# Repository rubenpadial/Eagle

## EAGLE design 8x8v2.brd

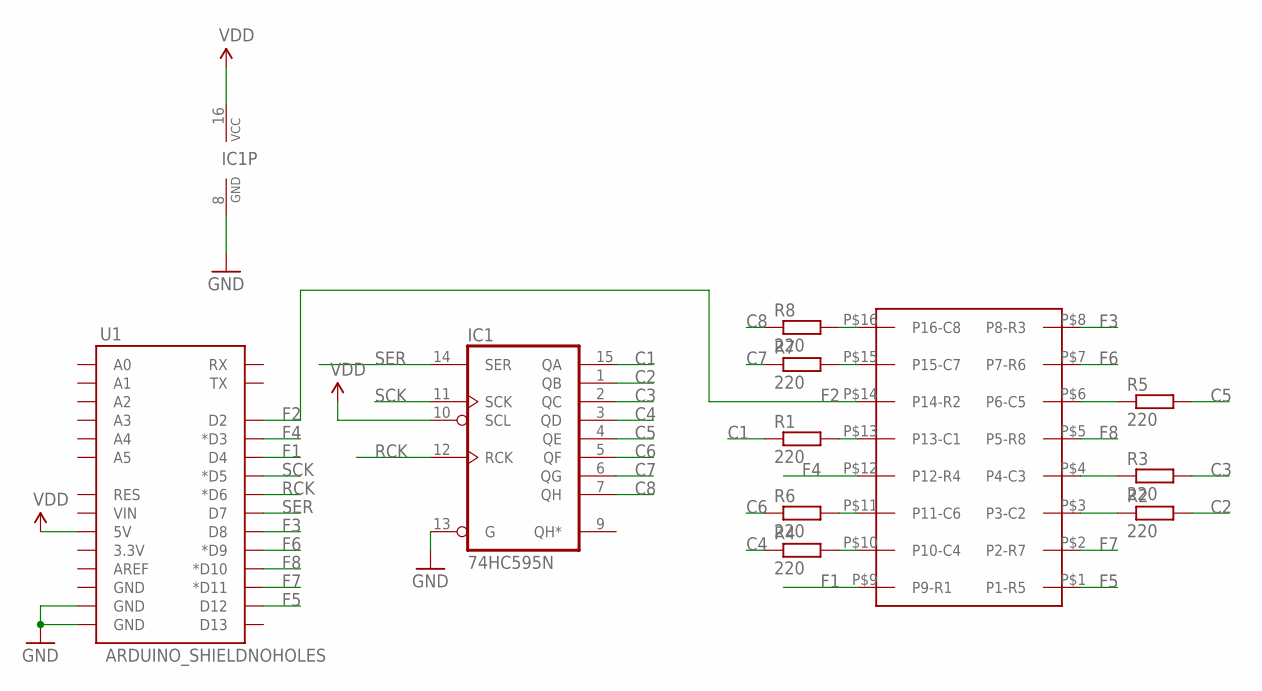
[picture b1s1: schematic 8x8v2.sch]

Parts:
IC1: 74HC595N; DIL16
R1, R2, R3, R4, R5, R6, R7, R8: 220; 0207/10
U1: ARDUINO_SHIELDNOHOLES; DUEMILANOVE_SHIELD_NOHOLES
U$1: MATRIX8X8; MATRIX

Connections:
C1: IC1.15 (QA), R1.1
C2: IC1.1 (QB), R2.2
C3: IC1.2 (QC), R3.2
C4: IC1.3 (QD), R4.1
C5: IC1.4 (QE), R5.2
C6: IC1.5 (QF), R6.1
C7: IC1.6 (QG), R7.1
C8: IC1.7 (QH), R8.1
F1: U1.D4, U$1.P$9 (P9-R1)
F2: U1.D2, U$1.P$14 (P14-R2)
F3: U1.D8, U$1.P$8 (P8-R3)
F4: U1.D3 (*D3), U$1.P$12 (P12-R4)
F5: U1.D12, U$1.P$1 (P1-R5)
F6: U1.D9 (*D9), U$1.P$7 (P7-R6)
F7: U1.D11 (*D11), U$1.P$2 (P2-R7)
F8: U1.D10 (*D10), U$1.P$5 (P5-R8)
GND: IC1.8 (GND), IC1.13 (G), U1.GND@0 (GND), U1.GND@1 (GND)
unnamed: R2.1, U$1.P$3 (P3-C2)
unnamed: R3.1, U$1.P$4 (P4-C3)
unnamed: R5.1, U$1.P$6 (P6-C5)
unnamed: R6.2, U$1.P$11 (P11-C6)
unnamed: R4.2, U$1.P$10 (P10-C4)
unnamed: R7.2, U$1.P$15 (P15-C7)
unnamed: R8.2, U$1.P$16 (P16-C8)
unnamed: R1.2, U$1.P$13 (P13-C1)
RCK: IC1.12 (RCK), U1.D6 (*D6)
SCK: IC1.11 (SCK), U1.D5 (*D5)
SER: IC1.14 (SER), U1.D7
VDD: IC1.10 (SCL), IC1.16 (VCC), U1.5V

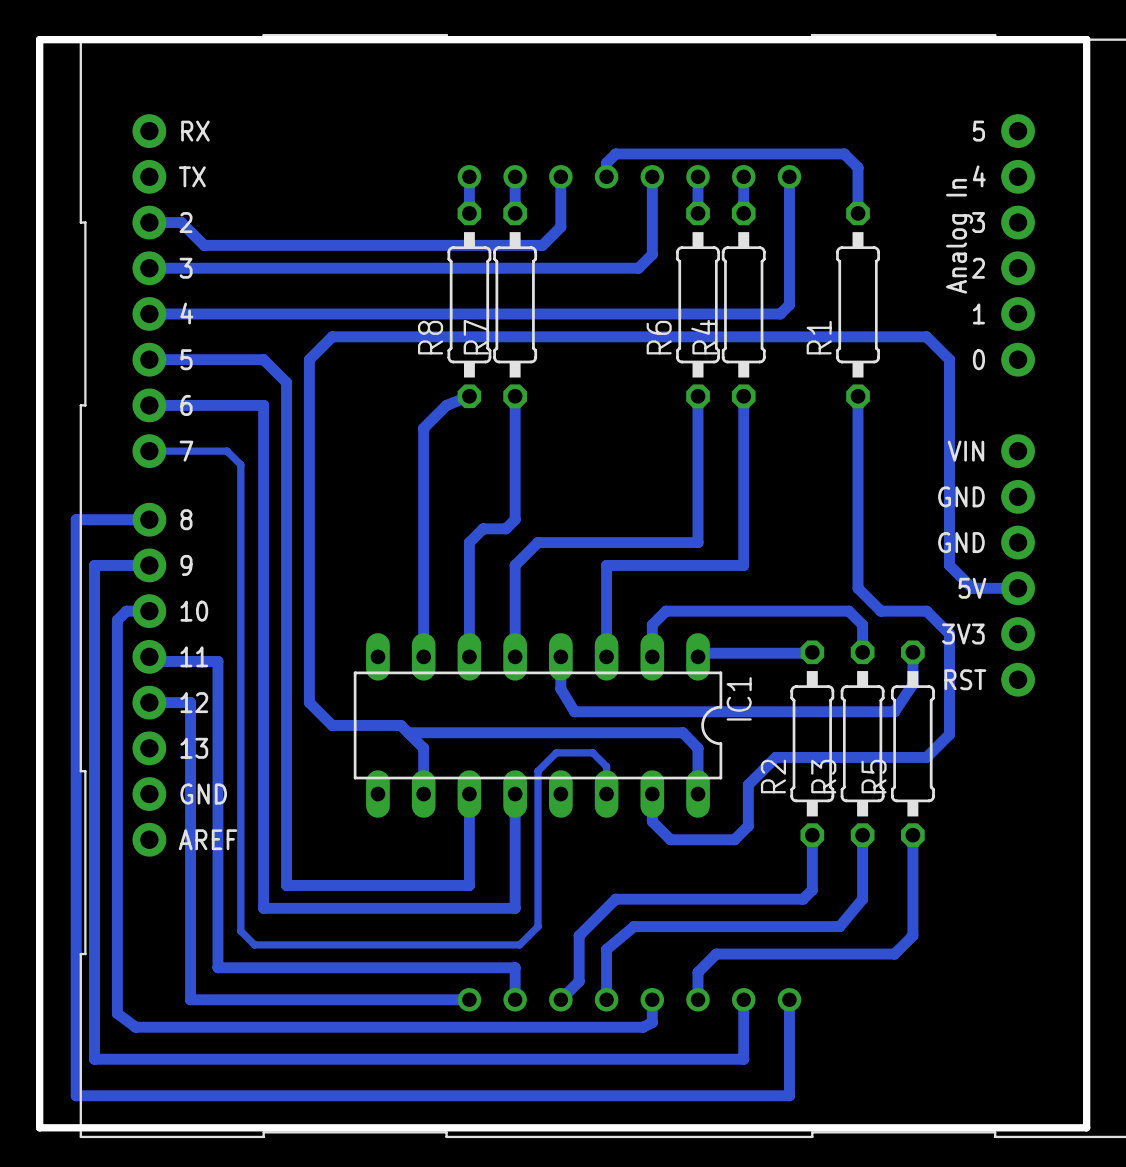
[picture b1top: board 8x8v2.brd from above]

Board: 2 copper layers, 58.2 x 60.5 mm, 11 parts (0 on the bottom side), 29 nets.

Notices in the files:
parts and their libraries:
SparkFun-Boards: Licensing: Creative Commons ShareAlike 4.0 International - https://creativecommons.org/licenses/by-sa/4.0
